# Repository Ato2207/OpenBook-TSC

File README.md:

# OpenBook-TSC

# 1. Diagrama bloc

# 2. Bill Of Materials (BOM)
| Nr. | Componentă                 | Cantitate | Link achiziție | Datasheet |
|----|-----------------------------|----------|-----------------|-----------|
| 1  | ESP32-C6-WROOM-1-N8         | 1        | [Mouser](https://ro.mouser.com/ProductDetail/Espressif-Systems/ESP32-C6-WROOM-1-N8?qs=8Wlm6%252BaMh8ST02Gmwp74cw%3D%3D) | [Datasheet](https://ro.mouser.com/datasheet/2/891/Espressif_ESP32_C6_WROOM_1__Datasheet_V0_1_PRELIMI-3239987.pdf) |
| 2  | Regulator de tensiune 3.3V  | 1        | [Mouser](https://www.mouser.co.uk/ProductDetail/Torex-Semiconductor/XC6220A331MR-G?qs=AsjdqWjXhJ8ZSWznL1J0gg%3D%3D) | [Datasheet](https://www.mouser.co.uk/datasheet/2/760/xc6220-3371556.pdf) |
| 3  | Display                     | 1        | https://www.waveshare.com/7.5inch-e-paper-hat.htm | [Datasheet](https://files.waveshare.com/upload/6/60/7.5inch_e-Paper_V2_Specification.pdf) |
| 4  | Senzor BME688 | 1        | [Mouser](https://ro.mouser.com/ProductDetail/Bosch-Sensortec/BME688?qs=IS%252B4QmGtzzqQoVDscqwx3A%3D%3D)| [Datasheet](https://ro.mouser.com/datasheet/2/783/bst_bme688_fl000-2307034.pdf) |
| 5  | Baterie            | 1        | [Mouser](https://www.tme.eu/ro/details/accu-lp584174_cl/acumulatori/cellevia-batteries/l584174/)| [Datasheet](https://www.tme.eu/Document/e0683d8c34e6d878124489f71bffb6ee/cel0014.pdf) |
| 6  | Fuel Gauge         | 1        | [Mouser](https://ro.mouser.com/ProductDetail/Analog-Devices-Maxim-Integrated/MAX17048G%2bT10?qs=D7PJwyCwLAoGnnn8jEPRBQ%3D%3D) | [Datasheet](https://ro.mouser.com/datasheet/2/609/MAX17048_MAX17049-3469099.pdf) |
| 7  | Controller de incarcare   | 1       | [Mouser](https://ro.mouser.com/ProductDetail/Microchip-Technology/MCP73831T-2ACI-MC?qs=yUQqVecv4quJ3ICqm%2FGZxw%3D%3D)| [Datasheet](https://ro.mouser.com/datasheet/2/268/MCP73831_Family_Data_Sheet_DS20001984H-3441711.pdf) |
| 8  | Butoane  | 3       | [Mouser](https://ro.mouser.com/ProductDetail/Panasonic/EVQ-Q2S03W?qs=WwqriLBepZso3gwmd6qd3A%3D%3D) | [Datasheet](https://4donline.ihs.com/images/VipMasterIC/IC/PANA/PANA-S-A0000770395/PANA-S-A0000770395-1.pdf?hkey=CECEF36DEECDED6468708AAF2E19C0C6) |
| 9  | Conector USB-C  | 1       | [Mouser](https://ro.mouser.com/ProductDetail/Amphenol-Commercial-Products/12401598E42A?qs=367PjNmvCmllVMBVyIyS3w%3D%3D) | [Datasheet](https://cdn.amphenol-cs.com/media/wysiwyg/files/documentation/datasheet/inputoutput/io_usb_type_c.pdf) |
| 10  | Conector card SD  | 1        | [Mouser](https://www.digikey.ro/en/products/detail/attend-technology/112A-TAAR-R03/17633923) | [Datasheet](https://www.attend.com.tw/data/download/file/112A-TAAR-R03_Spec.pdf) |
| 11  | RTC DS3231  | 1        | [Mouser](https://www.optimusdigital.ro/en/others/12402-ds3231-real-time-clock-module.html) | [Datasheet](https://www.analog.com/media/en/technical-documentation/data-sheets/ds3231.pdf) |
| 12  | Memorie Flash 64MB externa  | 1        | [Mouser](https://ro.mouser.com/ProductDetail/Winbond/W25Q512JVEIQ?qs=l7cgNqFNU1jw6svr3at6tA%3D%3D) | [Datasheet](https://ro.mouser.com/datasheet/2/949/Winbond_W25Q512JV_Datasheet-3240039.pdf) |
| 13 | Tranzistoare  | 3      | - | - |
| 14 | Diode | 10      | - | - |
| 15 | Condensatori diversi  | 28       | - | - |
| 16  | Rezistente diverse          | 24  | -  | - |

# 3. Functionalitate Hardware
  ## 3.1 Componente
  - **ESP32-C6-WROOM-1-N8** – Microcontroler principal care gestionează comunicațiile (SPI, I2C, UART) și controlează perifericele.  
  - **Conector USB-C & Protecție ESD** – Permite alimentarea prin USB-C și protejează circuitul de descărcările electrostatice.  
  - **Controler de Încărcare MCP73831** – Reglează încărcarea bateriei Li-Po și gestionează curentul de alimentare.  
  - **Baterie Li-Po** – Asigură alimentarea de rezervă pentru funcționare independentă de sursa USB.  
  - **Regulator de Tensiune LDO** – Stabilizează alimentarea la 3.3V pentru microcontroler și componente auxiliare.  
  - **Memorie Flash NOR Externă (64MB)** – Stocare suplimentară pentru date.
  - **Modul RTC DS3231SN** – Oferă funcționalitate de ceas în timp real, suportând alarme și detectarea pierderii tensiunii..  
  - **Senzor Ambiental BME688** – Măsoară temperatura, umiditatea, presiunea și calitatea aerului. Comunicare prin I2C, cu suport pentru conectare rapidă (Qwiic/Stemma QT).  
  - **E-Paper Display Drive Circuit si Header** – Genereaza semnalele necesare pentru controlul ecranului E-Paper.
  - **Slot SD Card** – Permite stocarea locală a datelor și fișierelor de configurare. 
  - **Supervizor de Tensiune + Butoane Reset/Boot** – Monitorizează alimentarea și asigură resetarea sistemului atunci când este necesar.

  ## 3.2 Specificatii de comunicare
  - **I2C** – Utilizat pentru senzorul BME688 și modulul DS3231SN.
  - **SPI** – Folosit pentru NOR Flash, display-ul E-Paper și cardul SD.
  - **UART** – Disponibil pentru debugging sau conectarea altor module. 
  - **Wi-Fi & Bluetooth LE** – Furnizate de ESP32-C6 pentru conectivitate wireless.

# 4. Pini ESP32-C6-WROOM-1-N8 si utilizare
| Pin ESP32-C6| Funcție              | Modul de utilizare                                     |
|-------------|----------------------|--------------------------------------------------------|
| **3V3**     | Supply               | Furnizează tensiune de 3.3V pentru componente.         |
| **GND**     | Ground               | Referință pentru circuit.                              |
| **EN**      | Enable               | Permite pornirea/resetarea modulului (tensiune ridicată = activ). |
| **IO0**     | Interrupt            | Pentru notificari, conectat la modulul RTC.            |
| **IO1**     | RTC CLK              | Semnal de ceas pentru modulul RTC.                     |
| **IO2**     | SPI MISO             | Primire date de la periferice conectate prin SPI.      |
| **IO3**     | Status               | Semnalizeaza starea de ocupay a display-ului.          |
| **IO4**     | Slave Select         | Selecteaza cardul SD.                                  |
| **IO5**     | Data/Command         | Selecteaza intre modul de date si comenzi.             |
| **IO6**     | SPI CLK              | Semnal de ceas pentru SPI.                             |
| **IO7**     | SPI MOSI             | Transfer date catre periferice conectate prin SPI.     |
| **IO8**     | GPIO                 | Pin general GPIO.                                      |
| **IO9**     | Boot                 | Conectat la un buton pentru intrarea in modul de boot. |
| **IO10**    | Chip Select          | Activeaza comunicarea cu display-ul.                   |
| **IO11**    | Chip Select          | Activeaza comunicarea cu memoria flash.                |    
| **IO12**    | USB_D-               | Pentru USB.                                            |
| **IO13**    | USB_D+               | Pentru USB.                                            |
| **IO15**    | Change               | Conectat la un buton.                                  |
| **IO16**    | TX                   | Pentru UART.                                           |
| **IO17**    | RX                   | Pentru UART.                                           |
| **IO18**    | RTC_RST              | Pentru resetarea modulului RTC.                        |
| **IO19**    | I2C_PW               | Supply pentru I2C.                                     |
| **IO20**    | EPD_3V3_C            | Alimentare display.                                    |
| **IO21**    | SDA                  | Linia de date pentru I2C.                              |
| **IO22**    | SCL                  | Semnalul de ceas pentru I2C.                           |
| **IO23**    | EPD_RST              | Pentru resetarea display-ului.                         |

# 4. Implementare

## 4.1 Documentatie
Am inceput prin a citi documentele puse la dispozitie, in ordinea data: MRD, PRD, ERD si documentul de Detailed Design si am extras anumite informatii utile referitoare la modul de functionare al device-ului.

## 4.2 Schematic
In continuare, prin comparare, am realizat schema electrica precum a fost data in cerinta, respectand toate constrangerile.Ulterior am facut si verificarea ERC si am rezolvat toate erorile semnalate, cu exceptia celor mentionate ca fiind acceptabile.

## 4.3 PCB
Dupa realizarea schemei electrice, am trecut la partea de board design, pastrand dimensiunile recomandate.Am amplasat componenetele exclusiv pe layer-ul TOP, respectand cu strictete pozitia celor care au contact cu exteriorul.Am realizat doua plane de masa(TOP & BOTTOM) si am aplicat via stitching, in special in jurul modulului ESP32.Am urmat constrangerile de rutare(DRC), inclusiv decuparea PCB-ului sub antena ESP32-ului pentru a nu ruta semnale in acea zona.In final, am realizat silkscreen-ul si am marcat toate test pad-urile cu numele semnalelor.

## 4.4 3D
Am importat carcasa data si am realizat modelul 3D al bateriei si al ecranului, desenate pe baza dimensiunilor din datasheet-uri.Avand toate piesele, le-am asezat in carcasa corespunzator pentru a nu avea suprapuneri si am aliniat PCB-ul cu mufa USB si slot-ul SD.

# 5. Dificultati intalnite si decizii luate

## Lipsa modele 3D
Pentru anumite componente nu am reusit sa gasesc chiar modelul 3D perfect, spre exemplu la butoane, card SD, connector-ul QWIIC, asa ca am ales sa merg pe ceva apropiat.

## Erori
Footprint-ul mufei USB are 2 erori de "Smd-Hole, Board Outline Clearance" cauzate de faptul ca gaurile de sustinere a componentei sunt prea apropiate de pini, conform fisierului de constrangeri.Astfel, am decis sa le aprob deoarece nu depindeau de mine.

## Vias-uri
Am incercat pe cat posibil sa evit folosirea vias-urilor la traseele de putere si aproape am reusit in totalitate, avand nevoie doar de unul singur la semnalul de VBAT.

## Display
Am realizat display-ul conform dimensiunilor din datasheet, dar acesta nu se potrivea in carcasa, asa ca am fost nevoit sa il fac independent de acele valori.

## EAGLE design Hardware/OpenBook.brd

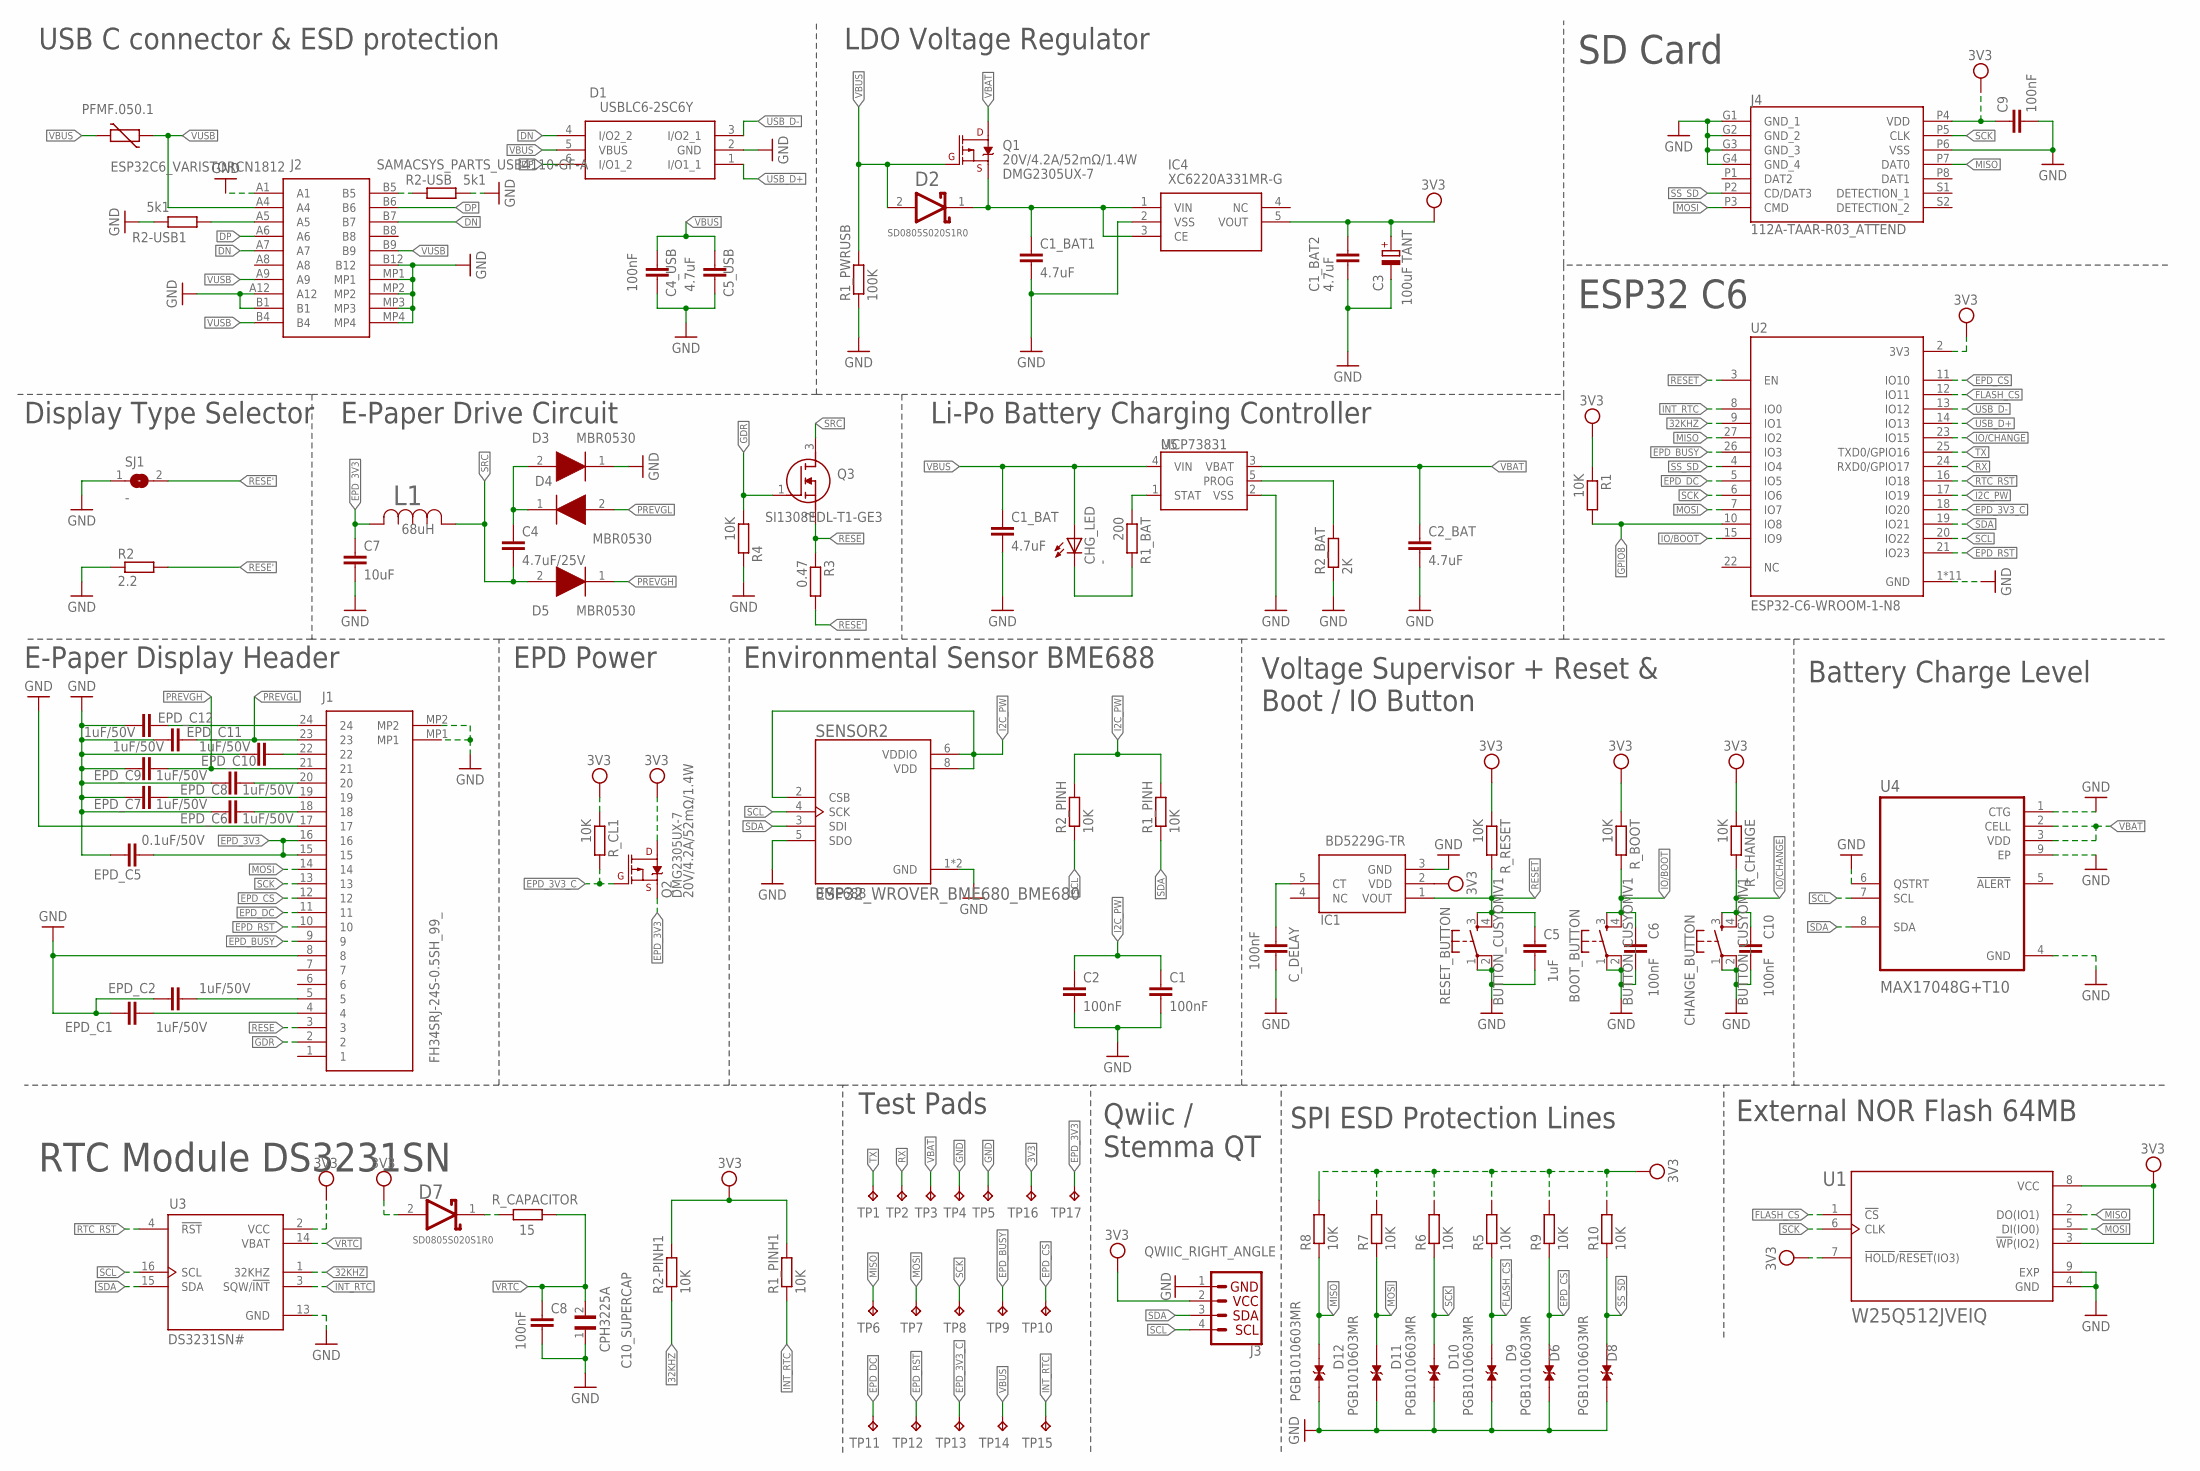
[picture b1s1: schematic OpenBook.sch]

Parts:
BOOT_BUTTON: BUTTON_CUSYOMV1; MYBUTTON
C1, C2, C4_USB, C6, C8, C9, C10: 100nF; EAGLE-LTSPICE_C0402
C1_BAT, C1_BAT1, C1_BAT2, C2_BAT, C5_USB: 4.7uF; EAGLE-LTSPICE_C0402
C3: 100uF TANT; RCL_CT3528
C4: 4.7uF/25V; EAGLE-LTSPICE_C0402
C5: 1uF; EAGLE-LTSPICE_C0402
C7: 10uF; EAGLE-LTSPICE_C0402
C10_SUPERCAP: CPH3225A; CAPCP3225X100N
CHANGE_BUTTON: BUTTON_CUSYOMV1; MYBUTTON
CHG_LED: -; ADAFRUIT_CHIP-LED0603
C_DELAY: 100nF; EAGLE-LTSPICE_C0402
D1: USBLC6-2SC6Y; SOT95P280X145-6N
D2: SD0805S020S1R0; ESP32_WROVER_AVX---SD0805S020S1R0_AVX_SD0805S020S1R0_0
D3, D4, D5: MBR0530; SOD3716X135N
D6, D8, D9, D10, D11, D12: PGB1010603MR; DIOC1608X36N
D7: ESP32_WROVER_AVX---SD0805S020S1R0_AVX_SD0805S020S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; ESP32_WROVER_AVX---SD0805S020S1R0_AVX_SD0805S020S1R0_0
EPD_C1, EPD_C2, EPD_C6, EPD_C7, EPD_C8, EPD_C9, EPD_C10, EPD_C11, EPD_C12: 1uF/50V; EAGLE-LTSPICE_C0402
EPD_C5: 0.1uF/50V; EAGLE-LTSPICE_C0402
IC1: BD5229G-TR; SOT95P280X125-5N
IC4: XC6220A331MR-G; SOT95P280X120-5N
J1: FH34SRJ-24S-0.5SH_99_; FH34SRJ24S05SH99
J2: SAMACSYS_PARTS_USB4110-GF-A; SAMACSYS_PARTS_USB4110GFA
J3: QWIIC_RIGHT_ANGLE; JST04_1MM_RA
J4: 112A-TAAR-R03_ATTEND; 112ATAARR03ATTEND
L1: 68uH; IND_4828-WE-TPC_WRE
PFMF.050.1: ESP32C6_VARISTORCN1812; ESP32C6_VARISTOR_CT/CN1812
Q1, Q2: 20V/4.2A/52mΩ/1.4W; ESP32_WROVER_SPARKFUN-DISCRETESEMI_SOT23-3
Q3: SI1308EDL-T1-GE3; SOT65P210X110-3N
R1, R1_PINH, R1_PINH1, R2-PINH1, R2_PINH, R4, R5, R6, R7, R8, R9, R10: 10K; ESP32_WROVER_EAGLE-LTSPICE_R0402
R1_BAT: 200; ESP32_WROVER_EAGLE-LTSPICE_R0402
R1_PWRUSB: 100K; ESP32_WROVER_EAGLE-LTSPICE_R0402
R2: 2.2; ESP32_WROVER_EAGLE-LTSPICE_R0402
R2-USB, R2-USB1: 5k1; ESP32_WROVER_EAGLE-LTSPICE_R0402
R2_BAT: 2K; ESP32_WROVER_EAGLE-LTSPICE_R0402
R3: 0.47; ESP32_WROVER_EAGLE-LTSPICE_R0402
RESET_BUTTON: BUTTON_CUSYOMV1; MYBUTTON
R_BOOT: 10K; ESP32_WROVER_EAGLE-LTSPICE_R0402
R_CAPACITOR: 15; ESP32_WROVER_EAGLE-LTSPICE_R0402
R_CHANGE: 10K; ESP32_WROVER_EAGLE-LTSPICE_R0402
R_CL1: 10K; ESP32_WROVER_EAGLE-LTSPICE_R0402
R_RESET: 10K; ESP32_WROVER_EAGLE-LTSPICE_R0402
SENSOR2: ESP32_WROVER_BME680_BME680; ESP32_WROVER_BME680_PSON80P300X300X100-8N
SJ1: -; SJ
TP1, TP2, TP3, TP4, TP5, TP6, TP7, TP8, TP9, TP10, TP11, TP12, TP13, TP14, TP15, TP16, TP17: TPTP20R; TP20R
U1: W25Q512JVEIQ; SON127P600X800X80-9N
U2: ESP32-C6-WROOM-1-N8; XCVR_ESP32-C6-WROOM-1-N8
U3: DS3231SN#; SOIC127P1032X265-16N
U4: MAX17048G+T10; SON50P200X200X80-9N
U5: MCP73831; ESP32_WROVER_SPARKFUN-IC-POWER_SOT23-5

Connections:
3V3: C1_BAT2.1, C3.+, C9.1, D7.2 (ANODE), IC1.2 (VDD), IC4.5 (VOUT), J3.2, J4.P4 (VDD), Q2.3 (D), R1.1, R1_PINH1.2, R2-PINH1.2, R5.2, R6.2, R7.2, R8.2, R9.2, R10.2, R_BOOT.1, R_CHANGE.1, R_CL1.1, R_RESET.1, TP16.TP, U1.3 (!WP!(IO2)), U1.7 (!HOLD!/!RESET!(IO3)), U1.8 (VCC), U2.2 (3V3), U3.2 (VCC)
32KHZ: R2-PINH1.1, U2.9 (IO1), U3.1 (32KHZ)
DN: D1.4 (I/O2_2), J2.A7, J2.B7
DP: D1.6 (I/O1_2), J2.A6, J2.B6
EPD_3V3: C7.1, EPD_C5.1, J1.15, J1.16, L1.2, Q2.2 (S), TP17.TP
EPD_3V3_C: Q2.1 (G), R_CL1.2, TP13.TP, U2.18 (IO20)
EPD_BUSY: J1.9, TP9.TP, U2.26 (IO3)
EPD_CS: D6.1, J1.12, R9.1, TP10.TP, U2.11 (IO10)
EPD_DC: J1.11, TP11.TP, U2.5 (IO5)
EPD_RST: J1.10, TP12.TP, U2.21 (IO23)
FLASH_CS: D9.1, R5.1, U1.1 (!CS), U2.12 (IO11)
GDR: J1.2, Q3.1 (G), R4.1
GND: BOOT_BUTTON.1, BOOT_BUTTON.2, C1.2, C1_BAT.2, C1_BAT1.2, C1_BAT2.2, C2.2, C2_BAT.2, C3.-, C4_USB.2, C5.2, C5_USB.2, C6.2, C7.2, C8.2, C9.2, C10.2, C10_SUPERCAP.1, CHANGE_BUTTON.1, CHANGE_BUTTON.2, C_DELAY.2, D1.2 (GND), D3.1 (K), D6.2, D8.2, D9.2, D10.2, D11.2, D12.2, EPD_C1.2, EPD_C2.2, EPD_C5.2, EPD_C6.2, EPD_C7.2, EPD_C8.2, EPD_C9.2, EPD_C10.2, EPD_C11.2, EPD_C12.2, IC1.3 (GND), IC4.2 (VSS), J1.8, J1.17, J1.MP1, J1.MP2, J2.A1, J2.A12, J2.B1, J2.B12, J2.MP1, J2.MP2, J2.MP3, J2.MP4, J3.1, J4.G1 (GND_1), J4.G2 (GND_2), J4.G3 (GND_3), J4.G4 (GND_4), J4.P6 (VSS), R1_PWRUSB.1, R2.1, R2-USB.2, R2-USB1.1, R2_BAT.1, R4.2, RESET_BUTTON.1, RESET_BUTTON.2, SENSOR2.1 (GND), SENSOR2.5 (SDO), SENSOR2.7 (GND), SJ1.1, TP4.TP, TP5.TP, U1.4 (GND), U1.9 (EXP), U2.1 (GND), U2.28 (GND), U2.29_1 (GND), U2.29_2 (GND), U2.29_3 (GND), U2.29_4 (GND), U2.29_5 (GND), U2.29_6 (GND), U2.29_7 (GND), U2.29_8 (GND), U2.29_9 (GND), U3.13 (GND), U4.1 (CTG), U4.4 (GND), U4.6 (QSTRT), U4.9 (EP), U5.2 (VSS)
GPIO8: R1.2, U2.10 (IO8)
I2C_PW: C1.1, C2.1, R1_PINH.2, R2_PINH.2, SENSOR2.2 (CSB), SENSOR2.6 (VDDIO), SENSOR2.8 (VDD), U2.17 (IO19)
INT_RTC: R1_PINH1.1, TP15.TP, U2.8 (IO0), U3.3 (SQW/!INT)
IO/BOOT: BOOT_BUTTON.3, BOOT_BUTTON.4, C6.1, R_BOOT.2, U2.15 (IO9)
IO/CHANGE: C10.1, CHANGE_BUTTON.3, CHANGE_BUTTON.4, R_CHANGE.2, U2.23 (IO15)
MISO: D12.1, J4.P7 (DAT0), R8.1, TP6.TP, U1.2 (DO(IO1)), U2.27 (IO2)
MOSI: D11.1, J1.14, J4.P3 (CMD), R7.1, TP7.TP, U1.5 (DI(IO0)), U2.7 (IO7)
unnamed: EPD_C2.1, J1.5
unnamed: D7.1 (CATHODE), R_CAPACITOR.2
unnamed: C_DELAY.1, IC1.5 (CT)
unnamed: EPD_C1.1, J1.4
unnamed: EPD_C6.1, J1.18
unnamed: EPD_C7.1, J1.19
unnamed: EPD_C8.1, J1.20
unnamed: C4.1, D3.2 (A), D4.1 (K)
unnamed: EPD_C10.1, J1.22
unnamed: R2_BAT.2, U5.5 (PROG)
unnamed: EPD_C12.1, J1.24
unnamed: R1_BAT.1, U5.1 (STAT)
unnamed: CHG_LED.C, R1_BAT.2
unnamed: C1_BAT1.1, D2.1 (CATHODE), IC4.1 (VIN), IC4.3 (CE), Q1.2 (S)
unnamed: J2.B5, R2-USB.1
unnamed: J2.A5, R2-USB1.2
PREVGH: D5.1 (K), EPD_C9.1, J1.21
PREVGL: D4.2 (A), EPD_C11.1, J1.23
RESE: J1.3, Q3.2 (S), R3.1
RESE': R2.2, R3.2, SJ1.2
RESET: C5.1, IC1.1 (VOUT), RESET_BUTTON.3, RESET_BUTTON.4, R_RESET.2, U2.3 (EN)
RTC_RST: U2.16 (IO18), U3.4 (!RST)
RX: TP2.TP, U2.24 (RXD0/GPIO17)
SCK: D10.1, J1.13, J4.P5 (CLK), R6.1, TP8.TP, U1.6 (CLK), U2.6 (IO6)
SCL: J3.4, R2_PINH.1, SENSOR2.4 (SCK), U2.20 (IO22), U3.16 (SCL), U4.7 (SCL)
SDA: J3.3, R1_PINH.1, SENSOR2.3 (SDI), U2.19 (IO21), U3.15 (SDA), U4.8 (SDA)
SRC: C4.2, D5.2 (A), L1.1, Q3.3 (D)
SS_SD: D8.1, J4.P2 (CD/DAT3), R10.1, U2.4 (IO4)
TX: TP1.TP, U2.25 (TXD0/GPIO16)
USB_D+: D1.1 (I/O1_1), U2.14 (IO13)
USB_D-: D1.3 (I/O2_1), U2.13 (IO12)
VBAT: C2_BAT.1, Q1.3 (D), TP3.TP, U4.2 (CELL), U4.3 (VDD), U5.3 (VBAT)
VBUS: C1_BAT.1, C4_USB.1, C5_USB.1, CHG_LED.A, D1.5 (VBUS), D2.2 (ANODE), PFMF.050.1.2, Q1.1 (G), R1_PWRUSB.2, TP14.TP, U5.4 (VIN)
VRTC: C8.1, C10_SUPERCAP.2, R_CAPACITOR.1, U3.14 (VBAT)
VUSB: J2.A4, J2.A9, J2.B4, J2.B9, PFMF.050.1.1

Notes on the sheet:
SD Card
ESP32 C6
Battery Charge Level
External NOR Flash 64MB
SPI ESD Protection Lines
Qwiic / Stemma QT
Test Pads
RTC Module DS3231SN
Voltage Supervisor + Reset & Boot / IO Button
Environmental Sensor BME688
EPD Power
E-Paper Display Header
Display Type Selector
E-Paper Drive Circuit
Li-Po Battery Charging Controller
LDO Voltage Regulator
USB C connector & ESD protection

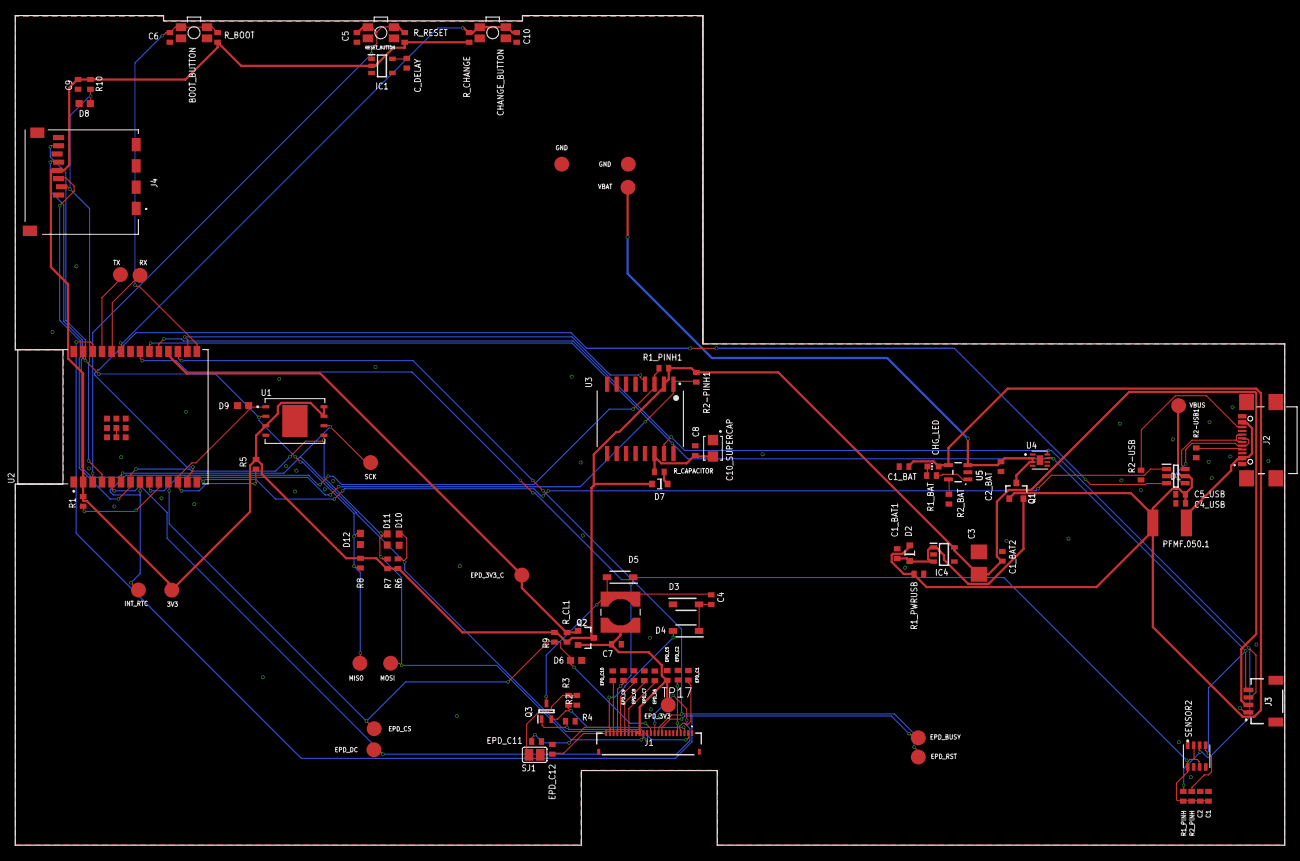
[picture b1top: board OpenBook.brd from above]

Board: 2 copper layers, 170.2 x 111.2 mm, 103 parts (0 on the bottom side), 55 nets.

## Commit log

2025-03-30 Update README.md, first 2 sections
2025-03-30 Update README.md, third section done, last is still WIP
2025-03-30 Update README.md, fixed typo
2025-03-30 Add manufacturing files
2025-03-30 Added gerbers to manufacturing folder
2025-03-30 Added Mechanical folder
2025-03-30 Add renders of the components and the full device
2025-04-04 Finished the entire design
2025-04-04 Reuploaded all files
2025-04-11 Solved some issues related to the 2d PCB
2025-04-11 Update README.md with 2 new sections

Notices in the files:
parts and their libraries:
COPYRIGHT: Copyright (C) 2024 Ultra Librarian. All rights reserved.
